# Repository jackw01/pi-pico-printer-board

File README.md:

# pi-pico-printer-board

## features

* Klipper compatible
* Uses Raspberry Pi Pico (RP2040)
* High reliability Weidmüller push-in connectors for all inputs and outputs
* 20A max and 7.5A max separately fused heater outputs
* 4x 3A max general purpose PWM outputs, individually configurable for 12V or 24V power, capable of driving inductive loads
* 3x thermistor inputs with 2.4Kohm pull up resistors
* 4x endstop inputs with one configurable for 5V or 12V operation for Z-probe
* 4x motor driver sockets
* Onboard 12V 3A and 5V 3A buck converters for powering accessories including Raspberry Pi
* Compatible with both 12V and 24V systems; components rated for 28V
* Compatible with both TMC2209 and A4988 motor drivers, and possibly others
* ESD and short-to-Vin protection on all microcontroller inputs
* Motor driver ESD and coil overvoltage protection
* Indicator LEDs for all power rails and outputs
* Alternatively supports 2.54mm pitch (Molex SL), or 2.5mm pitch (JST SM) headers for all inputs and outputs
* Labeled PCB for ease of setup and tinkering
* Open source PCB design

## design

[Schematic as PDF](pcb/rpi%20pico%20printer%20board%20rev1%2020241010.pdf)

[Sample Klipper Configuration File](klipper/printer.cfg)

[BOM (Excel)](pcb/bom.xlsx)

### license
This project is released under the CERN Open Hardware Licence Version 2 - Weakly Reciprocal (CERN-OHL-W V2).

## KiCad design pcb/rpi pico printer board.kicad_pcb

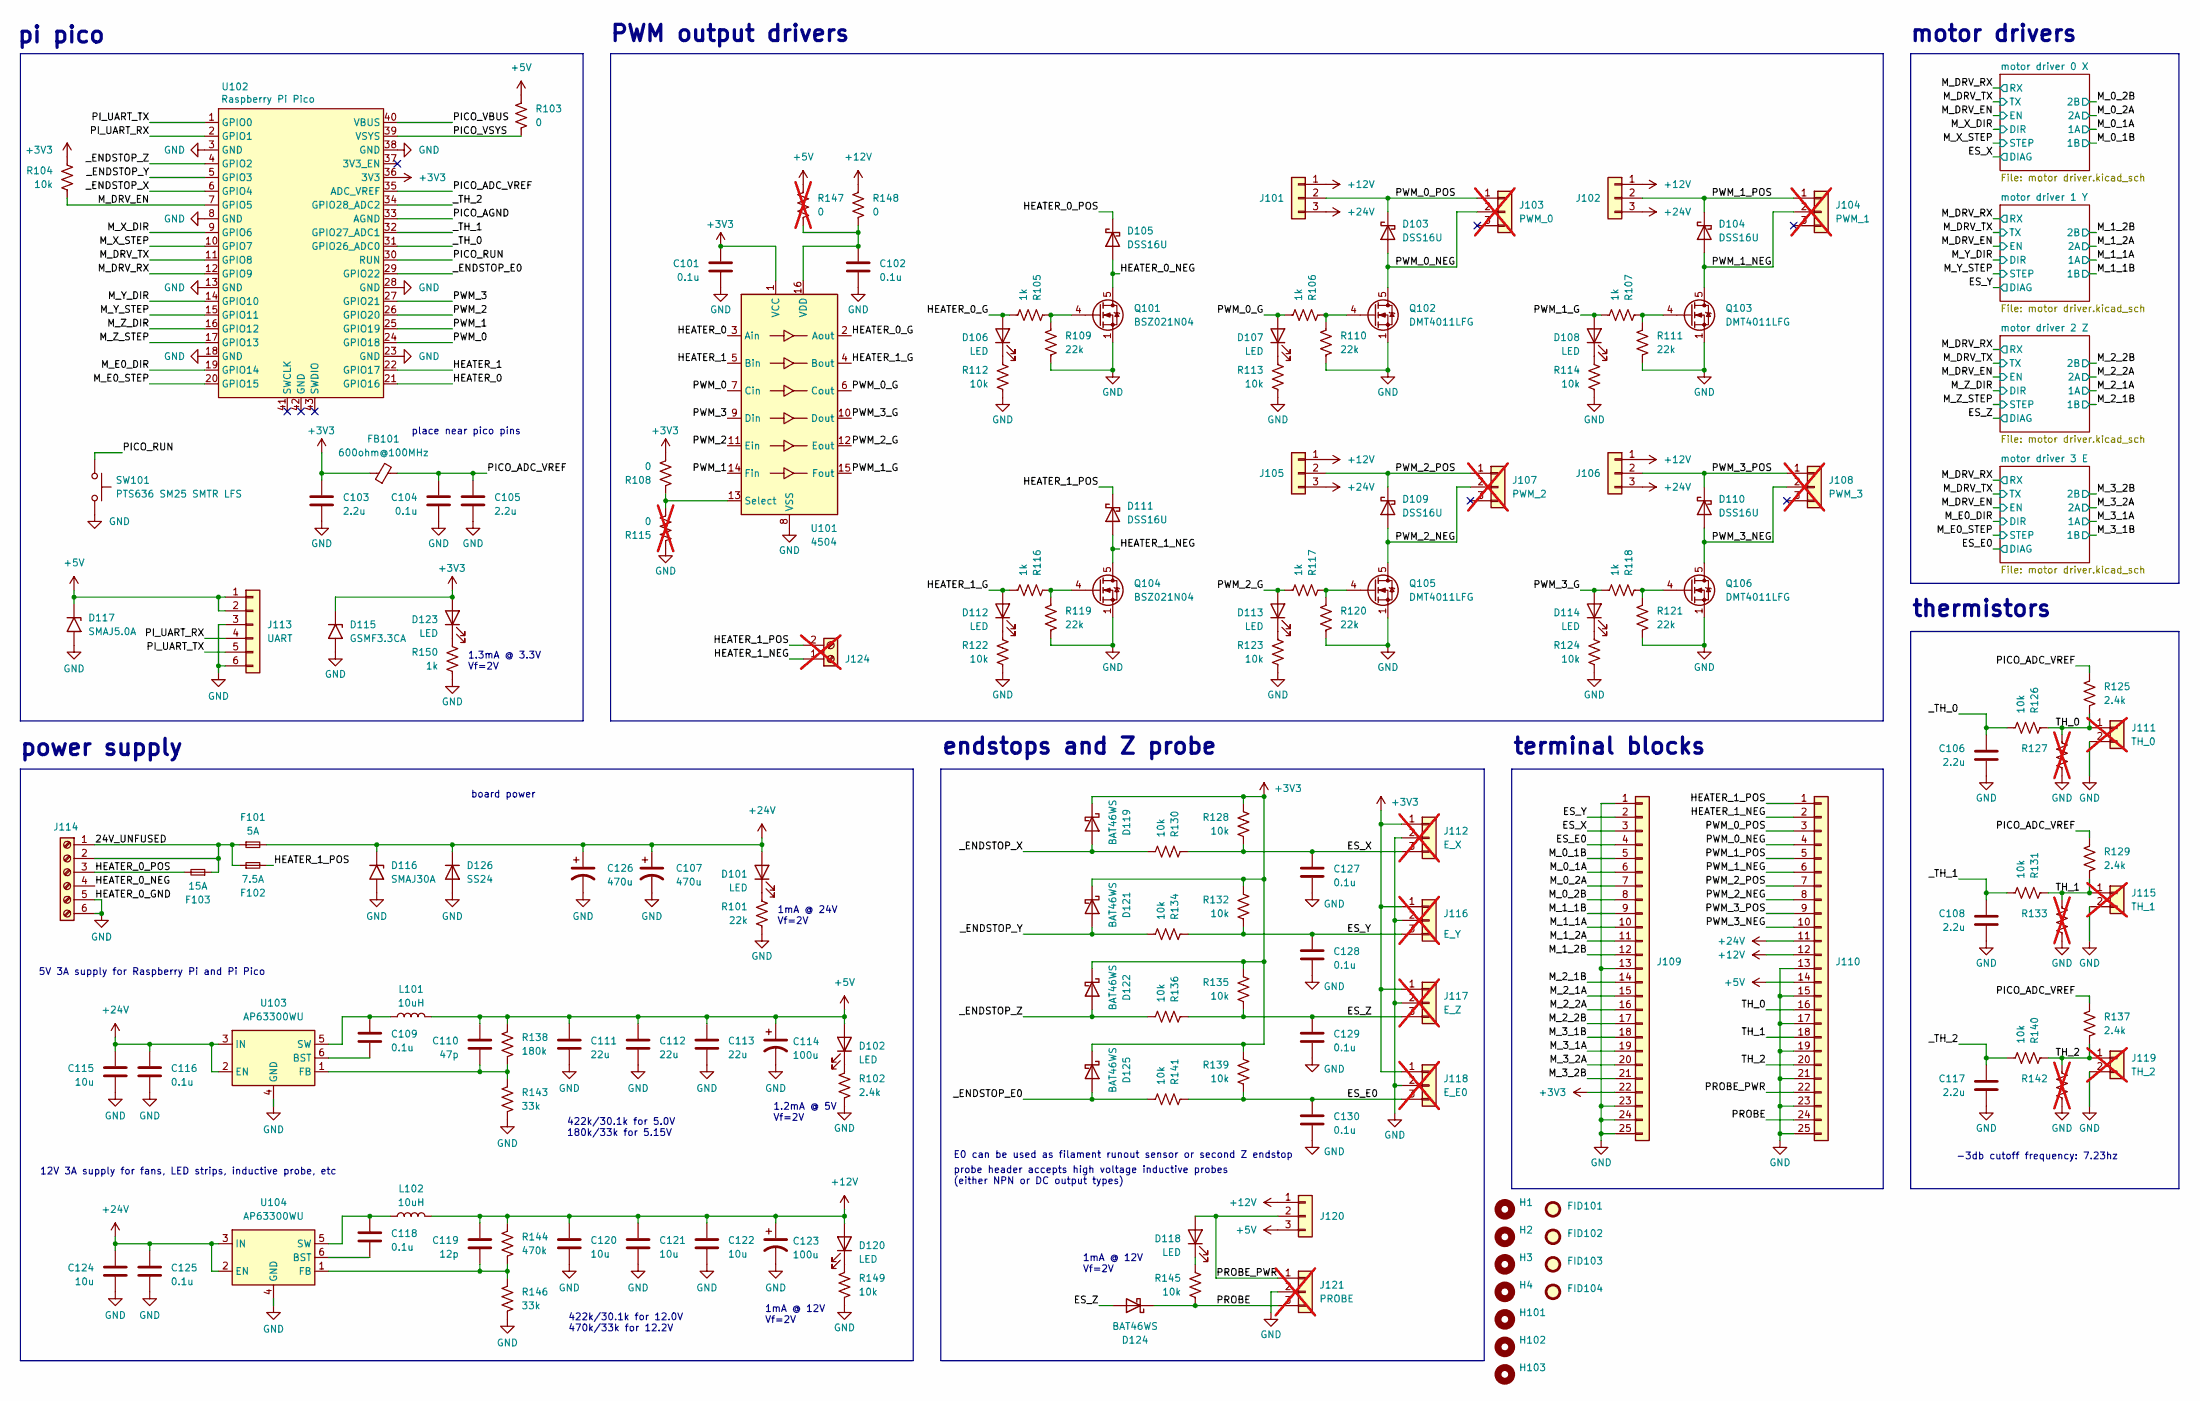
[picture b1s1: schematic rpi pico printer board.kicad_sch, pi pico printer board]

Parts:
C101, C102, C104, C109, C116, C118, C125, C127, C128, C129, C130: 0.1u; C_0603_1608Metric; MPN CL10B104KB8NNWC; JLCPCB Basic Part CC0603KRX7R9BB104
C103, C105, C106, C108, C117: 2.2u; C_0603_1608Metric; MPN CL10B225KP8NNNC; JLCPCB Basic Part CL10A225KO8NNNC
C107, C126: 470u; CP_Radial_D8.0mm_P3.50mm; MPN EEU-FR1V471L
C110: 47p; C_0603_1608Metric; MPN CL10C470JB8NNNC; JLCPCB Basic Part CL10C470JB8NNNC
C111, C112, C113: 22u; C_1210_3225Metric; MPN CL32B226KOJNNNE
C114, C123: 100u; CP_Radial_D6.3mm_P2.50mm; MPN ECA-1VM101
C115, C120, C121, C122, C124: 10u; C_1210_3225Metric; MPN CL32B106KBJNNNE
C119: 12p; C_0603_1608Metric; MPN CL10C120JB8NNNC; JLCPCB Basic Part CL10C120JB8NNNC
D101, D102, D106, D107, D108, D112, D113, D114, D118, D120, D123: LED; LED_0603_1608Metric_Pad1.05x0.95mm_HandSolder; MPN B1911UD--20D001014U1930; JLCPCB Basic Part KT-0603R
D103, D104, D105, D109, D110, D111: DSS16U; D_SOD-123F; MPN DSS16U; JLCPCB Basic Part DSK16
D115: GSMF3.3CA; D_SOD-123F; MPN GSMF3.3CA; JLCPCB Basic Part SMF3.3CA
D116: SMAJ30A; D_SMA; MPN SMAJ30A; JLCPCB Basic Part SMAJ30CA
D117: SMAJ5.0A; D_SMA; MPN SMAJ5.0A; JLCPCB Basic Part SMAJ5.0A
D119, D121, D122, D124, D125: BAT46WS; D_SOD-323; MPN BAT46WS; JLCPCB Basic Part BAT46WS
D126: SS24; D_SMA; MPN SS24; JLCPCB Basic Part SS24
F101: 5A; Fuseholder_Blade_Mini_Keystone_3568; MPN 3568
F102: 7.5A; Fuseholder_Blade_Mini_Keystone_3568; MPN 3568
F103: 15A; Fuseholder_Blade_Mini_Keystone_3568; MPN 3568
FB101: 600ohm@100MHz; L_0603_1608Metric; MPN BLM18AG601SH1D; JLCPCB Basic Part GZ1608D601TF
FID101, FID102, FID103, FID104: Fiducial_1mm_Mask2mm
H1, H2, H3, H4: MountingHole; MountingHole_3.2mm_M3_Mask
H101, H102, H103: ToolingHole; JLC_tooling_hole
J101, J102, J105, J106, J120: 2.54mm; PinHeader_1x03_P2.54mm_Vertical; MPN PH1-03-UA
J103: PWM_0; JST_XH_plus_2.54mm_01x03; not fitted
J104: PWM_1; JST_XH_plus_2.54mm_01x03; not fitted
J107: PWM_2; JST_XH_plus_2.54mm_01x03; not fitted
J108: PWM_3; JST_XH_plus_2.54mm_01x03; not fitted
J109, J110: Conn_01x25; Weidmuller_1870890000_25; MPN 1870630000
J111: TH_0; JST_XH_plus_2.54mm_01x02; not fitted
J112: E_X; JST_XH_plus_2.54mm_01x03; not fitted
J113: UART; Molex_SL_171971-0006_1x06_P2.54mm_Vertical; MPN 1719710006
J114: Screw_Terminal_01x06; Weidmuller_LMFV_5.00_06_90; MPN 2786570000
J115: TH_1; JST_XH_plus_2.54mm_01x02; not fitted
J116: E_Y; JST_XH_plus_2.54mm_01x03; not fitted
J117: E_Z; JST_XH_plus_2.54mm_01x03; not fitted
J118: E_E0; JST_XH_plus_2.54mm_01x03; not fitted
J119: TH_2; JST_XH_plus_2.54mm_01x02; not fitted
J121: PROBE; JST_XH_plus_2.54mm_01x03; not fitted
J124: Screw_Terminal_01x02; TerminalBlock_Phoenix_MKDS-1,5-2_1x02_P5.00mm_Horizontal; not fitted
L101, L102: 10uH; L_Bourns_SRN8040TA; MPN SRN8040TA-100M
Q101, Q104: BSZ021N04; Diodes_PowerDI3333-8; MPN BSZ021N04LS6ATMA1
Q102, Q103, Q105, Q106: DMT4011LFG; Diodes_PowerDI3333-8; MPN DMT4011LFG-13
R101, R109, R110, R111, R119, R120, R121: 22k; R_0603_1608Metric; JLCPCB Basic Part 0603WAF2202T5E
R102, R125, R129, R137: 2.4k; R_0603_1608Metric; JLCPCB Basic Part 0603WAF2401T5E
R103, R108, R148: 0; R_0603_1608Metric_Bridged
R104, R112, R113, R114, R122, R123, R124, R126, R128, R130, R131, R132, R134, R135, R136, R139, R140, R141, R145, R149: 10k; R_0603_1608Metric; JLCPCB Basic Part 0603WAF1002T5E
R105, R106, R107, R116, R117, R118, R150: 1k; R_0603_1608Metric; JLCPCB Basic Part 0603WAF1001T5E
R115, R147: 0; R_0603_1608Metric; not fitted
R127, R133, R142: R_0603_1608Metric; not fitted
R138: 180k; R_0603_1608Metric; JLCPCB Basic Part 0603WAF1803T5E
R143, R146: 33k; R_0603_1608Metric; JLCPCB Basic Part 0603WAF3302T5E
R144: 470k; R_0603_1608Metric; JLCPCB Basic Part 0603WAF4703T5E
SW101: PTS636 SM25 SMTR LFS; SW_SPST_CK_RS282G05A3; MPN PTS636 SM25 SMTR LFS
U101: 4504; TSSOP-16_4.4x5mm_P0.65mm; MPN CD4504BPWR
U102: Raspberry Pi Pico; RPi_Pico_SMD_minimal; MPN SC0915
U103, U104: AP63300WU; TSOT-23-6; MPN AP63300WU-7

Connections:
+3V3: C101.1, C103.1, D115.1 (A1), D119.1 (K), D121.1 (K), D122.1 (K), D123.2 (A), D125.1 (K), FB101.1, J109.22, J112.1, J116.1, J117.1, J118.1, R104.1, R108.2, R128.1, R132.1, R135.1, R139.1, U101.1 (VCC), U102.36 (3V3); also elsewhere on the board
+5V: C110.1, C111.1, C112.1, C113.1, C114.1, D102.2 (A), D117.1 (A1), J110.14, J113.1, J113.2, J120.3, L101.2, R103.1, R138.1, R147.1
+12V: C119.1, C120.1, C121.1, C122.1, C123.1, D120.2 (A), J101.1, J102.1, J105.1, J106.1, J110.12, J120.1, L102.2, R144.1, R148.1
+24V: C107.1, C115.1, C116.1, C124.1, C125.1, C126.1, D101.2 (A), D116.1 (A1), D126.1 (K), F101.2, J101.3, J102.3, J105.3, J106.3, J110.11, U103.2 (EN), U103.3 (IN), U104.2 (EN), U104.3 (IN); also elsewhere on the board
/24V_UNFUSED: F101.1, F102.1, F103.1, J114.1, J114.2
/ES_E0: C130.1, J109.4, J118.3, R139.2, R141.1; also elsewhere on the board
/ES_X: C127.1, J109.3, J112.3, R128.2, R130.1; also elsewhere on the board
/ES_Y: C128.1, J109.2, J116.3, R132.2, R134.1; also elsewhere on the board
/ES_Z: C129.1, D124.2 (A), J117.3, R135.2, R136.1; also elsewhere on the board
/HEATER_0: U101.3 (Ain), U102.21 (GPIO16)
/HEATER_0_G: D106.2 (A), R105.2, U101.2 (Aout)
/HEATER_0_NEG: D105.2 (A), J114.4, Q101.5 (D)
/HEATER_0_POS: D105.1 (K), F103.2, J114.3
/HEATER_1: U101.5 (Bin), U102.22 (GPIO17)
/HEATER_1_G: D112.2 (A), R116.2, U101.4 (Bout)
/HEATER_1_NEG: D111.2 (A), J110.2, J124.1, Q104.5 (D)
/HEATER_1_POS: D111.1 (K), F102.2, J110.1, J124.2
/M_0_1A: J109.6; also elsewhere on the board
/M_0_1B: J109.5; also elsewhere on the board
/M_0_2A: J109.7; also elsewhere on the board
/M_0_2B: J109.8; also elsewhere on the board
/M_1_1A: J109.10; also elsewhere on the board
/M_1_1B: J109.9; also elsewhere on the board
/M_1_2A: J109.11; also elsewhere on the board
/M_1_2B: J109.12; also elsewhere on the board
/M_2_1A: J109.15; also elsewhere on the board
/M_2_1B: J109.14; also elsewhere on the board
/M_2_2A: J109.16; also elsewhere on the board
/M_2_2B: J109.17; also elsewhere on the board
/M_3_1A: J109.19; also elsewhere on the board
/M_3_1B: J109.18; also elsewhere on the board
/M_3_2A: J109.20; also elsewhere on the board
/M_3_2B: J109.21; also elsewhere on the board
/M_DRV_EN: R104.2, U102.7 (GPIO5); also elsewhere on the board
/M_DRV_RX: U102.12 (GPIO9); also elsewhere on the board
/M_DRV_TX: U102.11 (GPIO8); also elsewhere on the board
/M_E0_DIR: U102.19 (GPIO14); also elsewhere on the board
/M_E0_STEP: U102.20 (GPIO15); also elsewhere on the board
/M_X_DIR: U102.9 (GPIO6); also elsewhere on the board
/M_X_STEP: U102.10 (GPIO7); also elsewhere on the board
/M_Y_DIR: U102.14 (GPIO10); also elsewhere on the board
/M_Y_STEP: U102.15 (GPIO11); also elsewhere on the board
/M_Z_DIR: U102.16 (GPIO12); also elsewhere on the board
/M_Z_STEP: U102.17 (GPIO13); also elsewhere on the board
/PICO_ADC_VREF: C104.1, C105.1, FB101.2, R125.1, R129.1, R137.1, U102.35 (ADC_VREF)
/PICO_AGND: U102.33 (AGND)
/PICO_RUN: SW101.1, U102.30 (RUN)
/PICO_VBUS: U102.40 (VBUS)
/PICO_VSYS: R103.2, U102.39 (VSYS)
/PI_UART_RX: J113.4, U102.2 (GPIO1)
/PI_UART_TX: J113.5, U102.1 (GPIO0)
/PROBE: D124.1 (K), J110.24, J121.3, R145.2
/PROBE_PWR: D118.2 (A), J110.22, J120.2, J121.1
/PWM_0: U101.7 (Cin), U102.24 (GPIO18)
/PWM_0_G: D107.2 (A), R106.2, U101.6 (Cout)
/PWM_0_NEG: D103.2 (A), J103.2, J110.4, Q102.5 (D)
/PWM_0_POS: D103.1 (K), J101.2, J103.1, J110.3
/PWM_1: U101.14 (Fin), U102.25 (GPIO19)
/PWM_1_G: D108.2 (A), R107.2, U101.15 (Fout)
/PWM_1_NEG: D104.2 (A), J104.2, J110.6, Q103.5 (D)
/PWM_1_POS: D104.1 (K), J102.2, J104.1, J110.5
/PWM_2: U101.11 (Ein), U102.26 (GPIO20)
/PWM_2_G: D113.2 (A), R117.2, U101.12 (Eout)
/PWM_2_NEG: D109.2 (A), J107.2, J110.8, Q105.5 (D)
/PWM_2_POS: D109.1 (K), J105.2, J107.1, J110.7
/PWM_3: U101.9 (Din), U102.27 (GPIO21)
/PWM_3_G: D114.2 (A), R118.2, U101.10 (Dout)
/PWM_3_NEG: D110.2 (A), J108.2, J110.10, Q106.5 (D)
/PWM_3_POS: D110.1 (K), J106.2, J108.1, J110.9
/TH_0: J110.16, J111.1, R125.2, R126.1, R127.1
/TH_1: J110.18, J115.1, R129.2, R131.1, R133.1
/TH_2: J110.20, J119.1, R137.2, R140.1, R142.1
/_ENDSTOP_E0: D125.2 (A), R141.2, U102.29 (GPIO22)
/_ENDSTOP_X: D119.2 (A), R130.2, U102.6 (GPIO4)
/_ENDSTOP_Y: D121.2 (A), R134.2, U102.5 (GPIO3)
/_ENDSTOP_Z: D122.2 (A), R136.2, U102.4 (GPIO2)
/_TH_0: C106.1, R126.2, U102.31 (GPIO26_ADC0)
/_TH_1: C108.1, R131.2, U102.32 (GPIO27_ADC1)
/_TH_2: C117.1, R140.2, U102.34 (GPIO28_ADC2)
GND: C101.2, C102.2, C103.2, C104.2, C105.2, C106.2, C107.2, C108.2, C111.2, C112.2, C113.2, C114.2, C115.2, C116.2, C117.2, C120.2, C121.2, C122.2, C123.2, C124.2, C125.2, C126.2, C127.2, C128.2, C129.2, C130.2, D115.2 (A2), D116.2 (A2), D117.2 (A2), D126.2 (A), J109.1, J109.13, J109.23, J109.24, J109.25, J110.13, J110.15, J110.17, J110.19, J110.21, J110.23, J110.25, J111.2, J112.2, J113.3, J113.6, J114.5, J114.6, J115.2, J116.2, J117.2, J118.2, J119.2, J121.2, Q101.1 (S), Q101.2 (S), Q101.3 (S), Q102.1 (S), Q102.2 (S), Q102.3 (S), Q103.1 (S), Q103.2 (S), Q103.3 (S), Q104.1 (S), Q104.2 (S), Q104.3 (S), Q105.1 (S), Q105.2 (S), Q105.3 (S), Q106.1 (S), Q106.2 (S), Q106.3 (S), R101.2, R102.2, R109.2, R110.2, R111.2, R112.2, R113.2, R114.2, R115.1, R119.2, R120.2, R121.2, R122.2, R123.2, R124.2, R127.2, R133.2, R142.2, R143.2, R146.2, R149.2, R150.2, SW101.2, U101.8 (VSS), U102.3 (GND), U102.8 (GND), U102.13 (GND), U102.18 (GND), U102.23 (GND), U102.28 (GND), U102.38 (GND), U103.4 (GND), U104.4 (GND); also elsewhere on the board
unnamed: D101.1 (K), R101.1
unnamed: D102.1 (K), R102.1
unnamed: D106.1 (K), R112.1
unnamed: D107.1 (K), R113.1
unnamed: D108.1 (K), R114.1
unnamed: D112.1 (K), R122.1
unnamed: D113.1 (K), R123.1
unnamed: D114.1 (K), R124.1
unnamed: D118.1 (K), R145.1
unnamed: D120.1 (K), R149.1
unnamed: D123.1 (K), R150.1
unnamed: Q101.4 (G), R105.1, R109.1
unnamed: Q102.4 (G), R106.1, R110.1
unnamed: Q103.4 (G), R107.1, R111.1
unnamed: Q104.4 (G), R116.1, R119.1
unnamed: Q105.4 (G), R117.1, R120.1
unnamed: Q106.4 (G), R118.1, R121.1
unnamed: R108.1, R115.2, U101.13 (Select)
unnamed: C102.1, R147.2, R148.2, U101.16 (VDD)
unnamed: C109.2, U103.6 (BST)
unnamed: C110.2, R138.2, R143.1, U103.1 (FB)
unnamed: C109.1, L101.1, U103.5 (SW)
unnamed: C118.2, U104.6 (BST)
unnamed: C119.2, R144.2, R146.1, U104.1 (FB)
unnamed: C118.1, L102.1, U104.5 (SW)

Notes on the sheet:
12V 3A supply for fans, LED strips, inductive probe, etc
motor drivers
PWM output drivers
1.2mA @ 5V Vf=2V
E0 can be used as filament runout sensor or second Z endstop
1.3mA @ 3.3V Vf=2V
board power
5V 3A supply for Raspberry Pi and Pi Pico
422k/30.1k for 12.0V 470k/33k for 12.2V
power supply
thermistors
terminal blocks
probe header accepts high voltage inductive probes (either NPN or DC output types)
1mA @ 12V Vf=2V
place near pico pins
1mA @ 24V Vf=2V
-3db cutoff frequency: 7.23hz
pi pico
endstops and Z probe
422k/30.1k for 5.0V 180k/33k for 5.15V

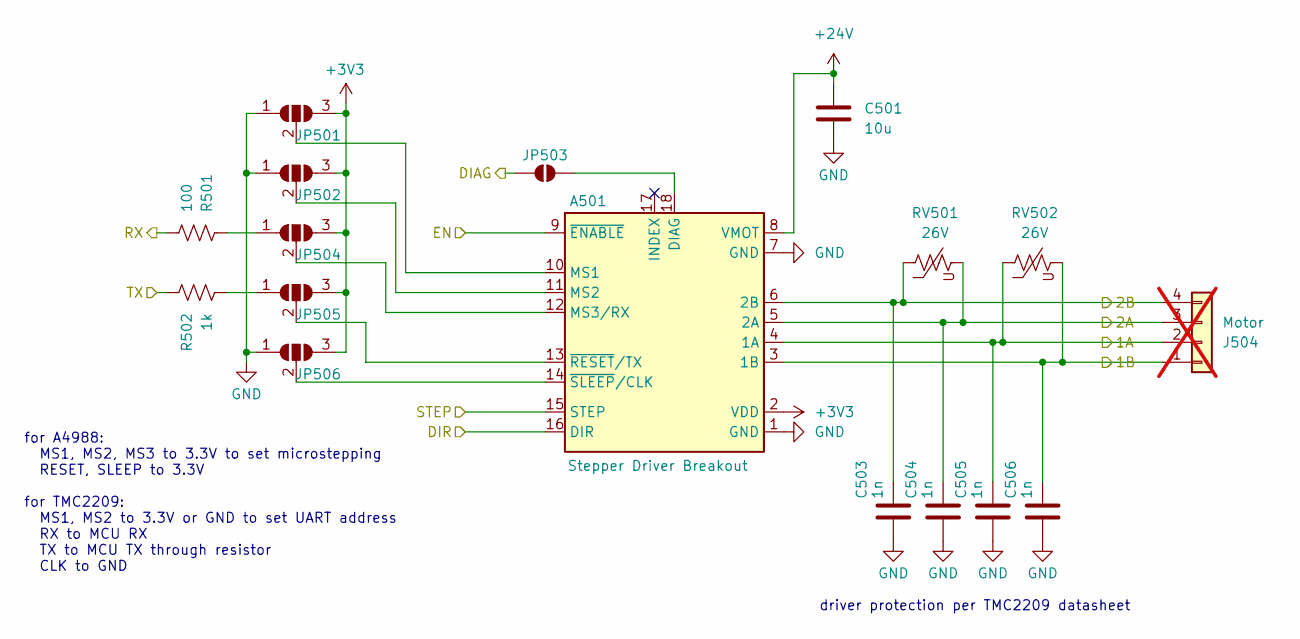
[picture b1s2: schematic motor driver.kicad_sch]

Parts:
A501: Stepper Driver Breakout; BTT_TMC2209_Breakout-16_15.2x20.3mm; MPN RS1-08-G
C501: 10u; C_1210_3225Metric; MPN CL32B106KBJNNNE
C503, C504, C505, C506: 1n; C_0603_1608Metric; MPN CL10B102KB8NNNC; JLCPCB Basic Part CL10B102KB8NNNC
J504: Motor; JST_XH_plus_2.54mm_01x04; not fitted
JP501, JP502, JP504, JP505, JP506: SolderJumper_3_Open; Bi_0603_Open
JP503: SolderJumper_2_Open; Jumper_0603
R501: 100; R_0603_1608Metric; JLCPCB Basic Part 0603WAF1000T5E
R502: 1k; R_0603_1608Metric; JLCPCB Basic Part 0603WAF1001T5E
RV501, RV502: 26V; L_1206_3216Metric; MPN ZV20K1206201NIR1

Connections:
+3V3: A501.2 (VDD), JP501.3 (B), JP502.3 (B), JP504.3 (B), JP505.3 (B), JP506.3 (B); also elsewhere on the board
+24V: A501.8 (VMOT), C501.1; also elsewhere on the board
/ES_E0: JP503.1 (A); also elsewhere on the board
/M_3_1A: A501.4 (1A), C505.2, J504.2, RV502.1; also elsewhere on the board
/M_3_1B: A501.3 (1B), C506.2, J504.1, RV502.2; also elsewhere on the board
/M_3_2A: A501.5 (2A), C504.2, J504.3, RV501.2; also elsewhere on the board
/M_3_2B: A501.6 (2B), C503.2, J504.4, RV501.1; also elsewhere on the board
/M_DRV_EN: A501.9 (~ENABLE); also elsewhere on the board
/M_DRV_RX: R501.2; also elsewhere on the board
/M_DRV_TX: R502.1; also elsewhere on the board
/M_E0_DIR: A501.16 (DIR); also elsewhere on the board
/M_E0_STEP: A501.15 (STEP); also elsewhere on the board
GND: A501.1 (GND), A501.7 (GND), C501.2, C503.1, C504.1, C505.1, C506.1, JP501.1 (A), JP502.1 (A), JP506.1 (A); also elsewhere on the board
unnamed: A501.18 (DIAG), JP503.2 (B)
unnamed: A501.10 (MS1), JP501.2 (C)
unnamed: A501.11 (MS2), JP502.2 (C)
unnamed: A501.12 (MS3/RX), JP504.2 (C)
unnamed: A501.13 (~RESET/TX), JP505.2 (C)
unnamed: A501.14 (~SLEEP/CLK), JP506.2 (C)
unnamed: JP504.1 (A), R501.1
unnamed: JP505.1 (A), R502.2

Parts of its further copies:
A201, A301, A401: Stepper Driver Breakout; BTT_TMC2209_Breakout-16_15.2x20.3mm; MPN RS1-08-G
C201, C301, C401: 10u; C_1210_3225Metric; MPN CL32B106KBJNNNE
C203, C204, C205, C206, C303, C304, C305, C306, C403, C404, C405, C406: 1n; C_0603_1608Metric; MPN CL10B102KB8NNNC; JLCPCB Basic Part CL10B102KB8NNNC
J204, J304, J404: Motor; JST_XH_plus_2.54mm_01x04; not fitted
JP201, JP202, JP204, JP205, JP206, JP301, JP302, JP304, JP305, JP306, JP401, JP402, JP404, JP405, JP406: SolderJumper_3_Open; Bi_0603_Open
JP203, JP303, JP403: SolderJumper_2_Open; Jumper_0603
R201, R301, R401: 100; R_0603_1608Metric; JLCPCB Basic Part 0603WAF1000T5E
R202, R302, R402: 1k; R_0603_1608Metric; JLCPCB Basic Part 0603WAF1001T5E
RV201, RV202, RV301, RV302, RV401, RV402: 26V; L_1206_3216Metric; MPN ZV20K1206201NIR1

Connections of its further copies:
+3V3: A201.2 (VDD), A301.2 (VDD), A401.2 (VDD), JP201.3 (B), JP202.3 (B), JP204.3 (B), JP205.3 (B), JP206.3 (B), JP301.3 (B), JP302.3 (B), JP304.3 (B), JP305.3 (B), JP306.3 (B), JP401.3 (B), JP402.3 (B), JP404.3 (B), JP405.3 (B), JP406.3 (B); also elsewhere on the board
+24V: A201.8 (VMOT), A301.8 (VMOT), A401.8 (VMOT), C201.1, C301.1, C401.1; also elsewhere on the board
/ES_X: JP203.1 (A); also elsewhere on the board
/ES_Y: JP303.1 (A); also elsewhere on the board
/ES_Z: JP403.1 (A); also elsewhere on the board
/M_0_1A: A201.4 (1A), C205.2, J204.2, RV202.1; also elsewhere on the board
/M_0_1B: A201.3 (1B), C206.2, J204.1, RV202.2; also elsewhere on the board
/M_0_2A: A201.5 (2A), C204.2, J204.3, RV201.2; also elsewhere on the board
/M_0_2B: A201.6 (2B), C203.2, J204.4, RV201.1; also elsewhere on the board
/M_1_1A: A301.4 (1A), C305.2, J304.2, RV302.1; also elsewhere on the board
/M_1_1B: A301.3 (1B), C306.2, J304.1, RV302.2; also elsewhere on the board
/M_1_2A: A301.5 (2A), C304.2, J304.3, RV301.2; also elsewhere on the board
/M_1_2B: A301.6 (2B), C303.2, J304.4, RV301.1; also elsewhere on the board
/M_2_1A: A401.4 (1A), C405.2, J404.2, RV402.1; also elsewhere on the board
/M_2_1B: A401.3 (1B), C406.2, J404.1, RV402.2; also elsewhere on the board
/M_2_2A: A401.5 (2A), C404.2, J404.3, RV401.2; also elsewhere on the board
/M_2_2B: A401.6 (2B), C403.2, J404.4, RV401.1; also elsewhere on the board
/M_DRV_EN: A201.9 (~ENABLE), A301.9 (~ENABLE), A401.9 (~ENABLE); also elsewhere on the board
/M_DRV_RX: R201.2, R301.2, R401.2; also elsewhere on the board
/M_DRV_TX: R202.1, R302.1, R402.1; also elsewhere on the board
/M_X_DIR: A201.16 (DIR); also elsewhere on the board
/M_X_STEP: A201.15 (STEP); also elsewhere on the board
/M_Y_DIR: A301.16 (DIR); also elsewhere on the board
/M_Y_STEP: A301.15 (STEP); also elsewhere on the board
/M_Z_DIR: A401.16 (DIR); also elsewhere on the board
/M_Z_STEP: A401.15 (STEP); also elsewhere on the board
GND: A201.1 (GND), A201.7 (GND), A301.1 (GND), A301.7 (GND), A401.1 (GND), A401.7 (GND), C201.2, C203.1, C204.1, C205.1, C206.1, C301.2, C303.1, C304.1, C305.1, C306.1, C401.2, C403.1, C404.1, C405.1, C406.1, JP201.1 (A), JP202.1 (A), JP206.1 (A), JP301.1 (A), JP302.1 (A), JP306.1 (A), JP401.1 (A), JP402.1 (A), JP406.1 (A); also elsewhere on the board
unnamed: A201.18 (DIAG), JP203.2 (B)
unnamed: A201.10 (MS1), JP201.2 (C)
unnamed: A201.11 (MS2), JP202.2 (C)
unnamed: A201.12 (MS3/RX), JP204.2 (C)
unnamed: A201.13 (~RESET/TX), JP205.2 (C)
unnamed: A201.14 (~SLEEP/CLK), JP206.2 (C)
unnamed: A301.18 (DIAG), JP303.2 (B)
unnamed: A301.10 (MS1), JP301.2 (C)
unnamed: A301.11 (MS2), JP302.2 (C)
unnamed: A301.12 (MS3/RX), JP304.2 (C)
unnamed: A301.13 (~RESET/TX), JP305.2 (C)
unnamed: A301.14 (~SLEEP/CLK), JP306.2 (C)
unnamed: A401.18 (DIAG), JP403.2 (B)
unnamed: A401.10 (MS1), JP401.2 (C)
unnamed: A401.11 (MS2), JP402.2 (C)
unnamed: A401.12 (MS3/RX), JP404.2 (C)
unnamed: A401.13 (~RESET/TX), JP405.2 (C)
unnamed: A401.14 (~SLEEP/CLK), JP406.2 (C)
unnamed: JP204.1 (A), R201.1
unnamed: JP205.1 (A), R202.2
unnamed: JP304.1 (A), R301.1
unnamed: JP305.1 (A), R302.2
unnamed: JP404.1 (A), R401.1
unnamed: JP405.1 (A), R402.2

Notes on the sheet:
driver protection per TMC2209 datasheet
for A4988: MS1, MS2, MS3 to 3.3V to set microstepping RESET, SLEEP to 3.3V for TMC2209: MS1, MS2 to 3.3V or GND to set UART address RX to MCU RX TX to MCU TX through resistor CLK to GND

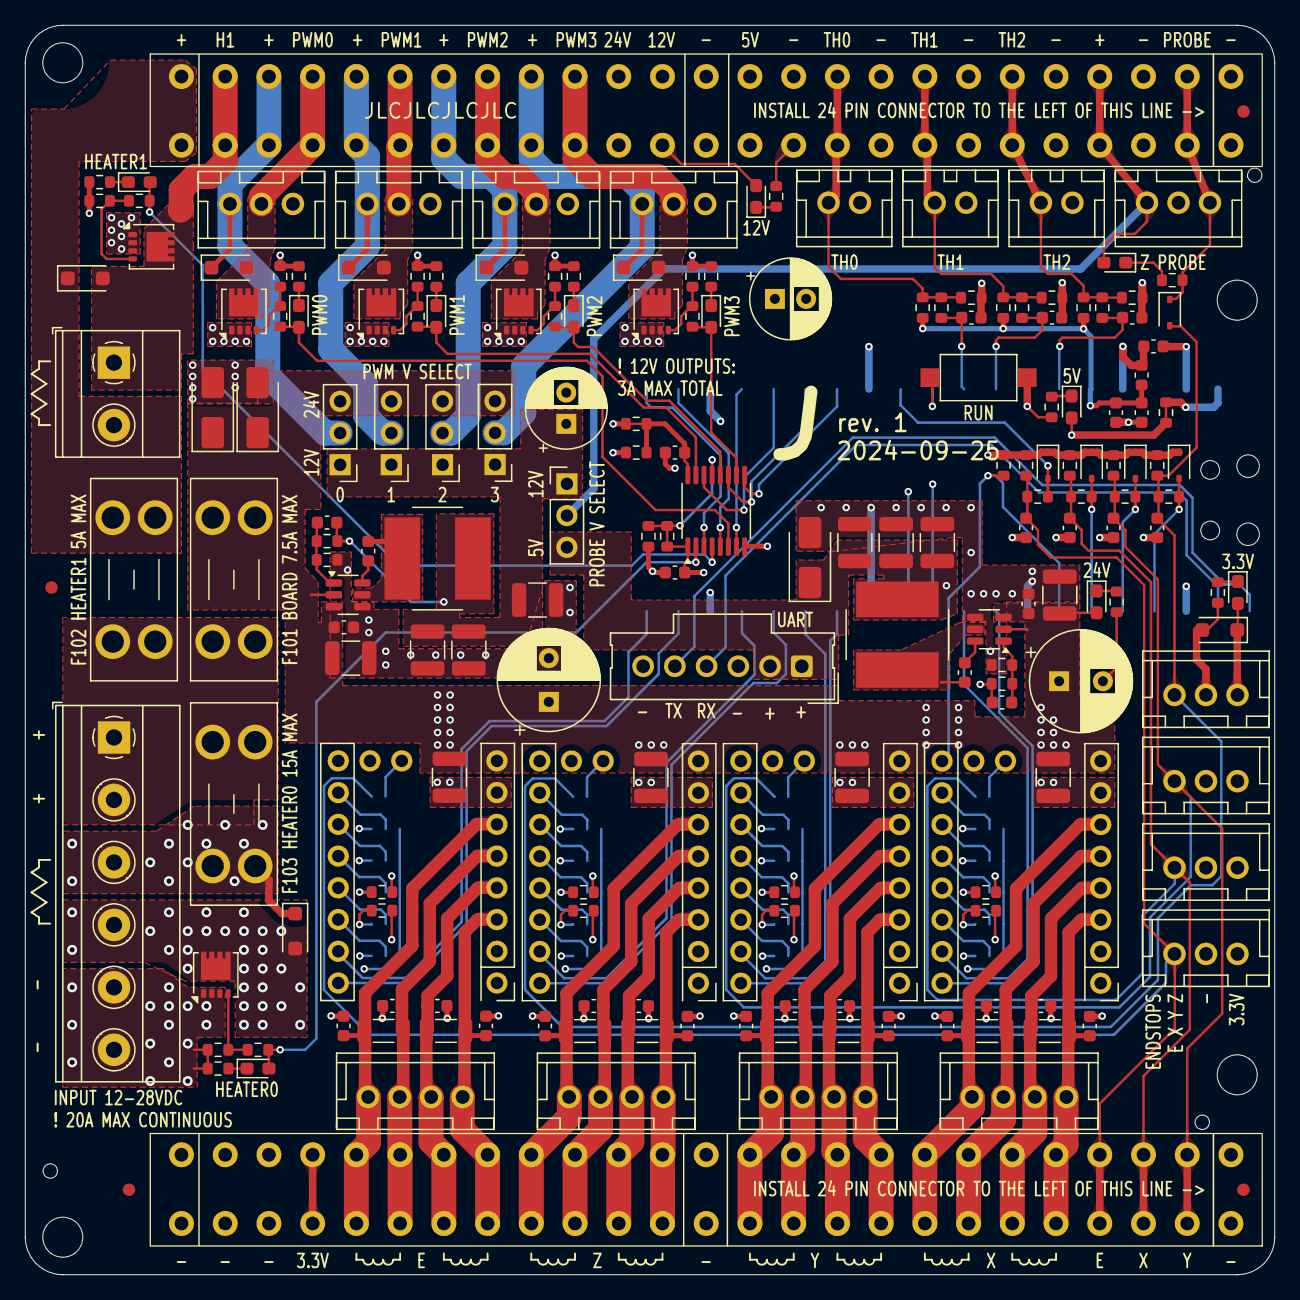
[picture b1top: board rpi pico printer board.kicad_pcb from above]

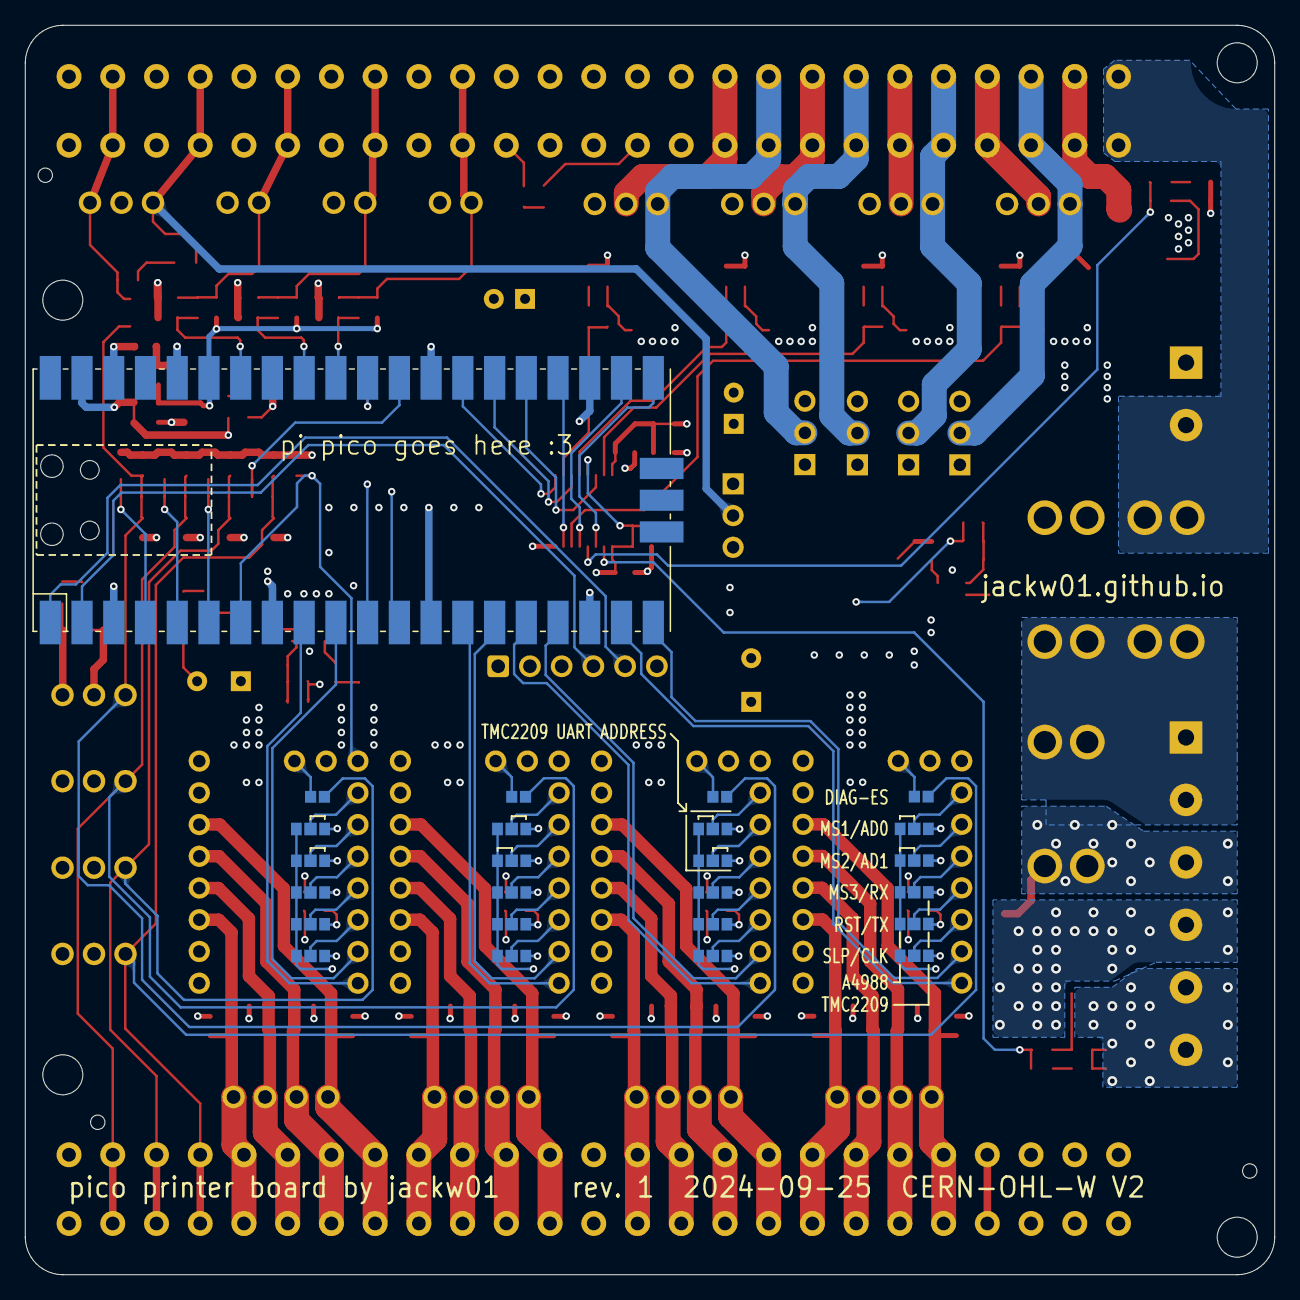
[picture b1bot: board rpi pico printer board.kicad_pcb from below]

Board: 4 copper layers, 100.0 x 100.0 mm, 224 parts (25 on the bottom side), 135 nets.

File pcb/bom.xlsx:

|  |  |  |  | 168 | 25 |  |  |  |  | 48.148500000000006 |  |  | 123.97999999999999
Reference | Value | Datasheet | Footprint | SMT | Qty | Qty THT | DNP | MPN | JLCPCB Basic/ExtPref | Cost | Ext. Cost Per Board | MOQ | Already Have? | Order Cost
A201,A301,A401,A501 | Stepper Driver Breakout | ~ | Custom:BTT_TMC2209_Breakout-16_15.2x20.3mm |  | 8 | 8 |  | RS1-08-G |  | 0.43 | 3.44 | 17 |  | 7.31
C101,C102,C104,C109,C116,C118,C125,C127,C128,C129,C130 | 0.1u | ~ | Capacitor_SMD:C_0603_1608Metric | Y | 11 | 0 |  | CL10B104KB8NNWC | CC0603KRX7R9BB104 | 7.9000000000000008E-3 | 8.6900000000000005E-2 | 100 |  | 0
C103,C105,C106,C108,C117 | 2.2u | ~ | Capacitor_SMD:C_0603_1608Metric | Y | 5 | 0 |  | CL10B225KP8NNNC | CL10A225KO8NNNC | 4.1000000000000002E-2 | 0.20500000000000002 | 50 |  | 0
C107,C126 | 470u | ~ | Capacitor_THT:CP_Radial_D8.0mm_P3.50mm |  | 2 | 2 |  | EEU-FR1V471L |  | 0.45100000000000001 | 0.90200000000000002 | 10 |  | 4.51
C110 | 47p | ~ | Capacitor_SMD:C_0603_1608Metric | Y | 1 | 0 |  | CL10C470JB8NNNC | CL10C470JB8NNNC | 3.4000000000000002E-2 | 3.4000000000000002E-2 | 10 |  | 0
C111,C112,C113 | 22u | ~ | Capacitor_SMD:C_1210_3225Metric | Y | 3 | 0 |  | CL32B226KOJNNNE |  | 0.29499999999999998 | 0.88500000000000001 | 10 |  | 2.9499999999999997
C114,C123 | 100u | ~ | Capacitor_THT:CP_Radial_D6.3mm_P2.50mm |  | 2 | 2 |  | ECA-1VM101 |  | 0.19 | 0.38 | 10 |  | 1.9
C115,C120,C121,C122,C124,C201,C301,C401,C501 | 10u | ~ | Capacitor_SMD:C_1210_3225Metric | Y | 9 | 0 |  | CL32B106KBJNNNE |  | 0.28060000000000002 | 2.5254000000000003 | 50 |  | 14.030000000000001
C119 | 12p | ~ | Capacitor_SMD:C_0603_1608Metric | Y | 1 | 0 |  | CL10C120JB8NNNC | CL10C120JB8NNNC | 2.1999999999999999E-2 | 2.1999999999999999E-2 | 10 |  | 0
C203,C204,C205,C206,C303,C304,C305,C306,C403,C404,C405,C406,C503,C504,C505,C506 | 1n | ~ | Capacitor_SMD:C_0603_1608Metric | Y | 16 | 0 |  | CL10B102KB8NNNC | CL10B102KB8NNNC | 1.2200000000000001E-2 | 0.19520000000000001 | 100 |  | 0
D101,D102,D106,D107,D108,D112,D113,D114,D118,D120,D123 | LED | ~ | LED_SMD:LED_0603_1608Metric_Pad1.05x0.95mm_HandSolder | Y | 11 | 0 |  | B1911UD--20D001014U1930 | KT-0603R | 4.7E-2 | 0.51700000000000002 | 10 |  | 0
D103,D104,D105,D109,D110,D111 | DSS16U | ~ | Diode_SMD:D_SOD-123 | Y | 6 | 0 |  | DSS16U | DSK16 | 0.11899999999999999 | 0.71399999999999997 | 10 |  | 0
D115 | D3V3AP2W | ~ | Diode_SMD:D_SOD-123 | Y | 1 | 0 |  | GSMF3.3CA |  | 0.13400000000000001 | 0.13400000000000001 | 10 |  | 1.34
D116 | SMAJ30A | ~ | Diode_SMD:D_SMA | Y | 1 | 0 |  | SMAJ30A | SMAJ30CA | 0.39 | 0.39 | 1 |  | 0
D117 | SMAJ5.0A | ~ | Diode_SMD:D_SMA | Y | 1 | 0 |  | SMAJ5.0A | SMAJ5.0A | 0.39 | 0.39 | 1 |  | 0
D119,D121,D122,D124,D125 | BAT46WS | ~ | Diode_SMD:D_SOD-323 | Y | 5 | 0 |  | BAT46WS | BAT46WS | 0.13900000000000001 | 0.69500000000000006 | 10 |  | 0
D126 | SS24 | ~ | Diode_SMD:D_SMA | Y | 1 | 0 |  | SS24 | SS24 | 0.26700000000000002 | 0.26700000000000002 | 10 |  | 0
F101 | 5A | ~ | Fuse:Fuseholder_Blade_Mini_Keystone_3568 |  | 1 | 1 |  | 3568 |  | 1.31 | 1.31 | 1 |  | 2.62
F102 | 7.5A | ~ | Fuse:Fuseholder_Blade_Mini_Keystone_3568 |  | 1 | 1 |  | 3568 |  | 1.31 | 1.31 | 1 |  | 2.62
F103 | 15A | ~ | Fuse:Fuseholder_Blade_Mini_Keystone_3568 |  | 1 | 1 |  | 3568 |  | 1.31 | 1.31 | 1 |  | 2.62
FB101 | 600ohm@100MHz | ~ | Inductor_SMD:L_0603_1608Metric | Y | 1 | 0 |  | BLM18AG601SH1D | GZ1608D601TF | 7.0999999999999994E-2 | 7.0999999999999994E-2 | 10 |  | 0
J101,J102,J105,J106,J120 | 2.54mm | ~ | Connector_PinHeader_2.54mm:PinHeader_1x03_P2.54mm_Vertical |  | 5 | 5 |  | PH1-03-UA |  | 4.7E-2 | 0.23499999999999999 | 10 |  | 0.47
J109,J110 | Conn_01x25 | ~ | Custom:Weidmuller_1870890000_25 |  | 2 | 2 |  | 1870630000 |  | 5.55 | 11.1 | 1 |  | 22.2
J113 | UART | ~ | Custom:Molex_SL_171971-0006_1x06_P2.54mm_Vertical |  | 1 | 1 |  | 1719710006 |  | 1.43 | 1.43 | 1 |  | 2.86
J114 | Screw_Terminal_01x06 | ~ | Custom:Weidmuller_LMFV_5.00_06_90 |  | 1 | 1 |  | 2786570000 |  | 4.26 | 4.26 | 1 |  | 8.52
L101,L102 | 10uH | ~ | Custom:L_Bourns_SRN8040TA | Y | 2 | 0 |  | SRN8040TA-100M |  | 0.55200000000000005 | 1.1040000000000001 | 10 |  | 5.5200000000000005
Q101,Q104 | BSZ021N04 |  | Package_SON:Diodes_PowerDI3333-8 | Y | 2 | 0 |  | BSZ021N04LS6ATMA1 |  | 1.5660000000000001 | 3.1320000000000001 | 10 |  | 15.66
Q102,Q103,Q105,Q106 | DMT4011LFG |  | Package_SON:Diodes_PowerDI3333-8 | Y | 4 | 0 |  | DMT4011LFG-13 |  | 0.442 | 1.768 | 10 |  | 4.42
R101,R109,R110,R111,R119,R120,R121 | 22k | ~ | Resistor_SMD:R_0603_1608Metric | Y | 7 | 0 |  |  | 0603WAF2202T5E | 7.7999999999999996E-3 | 5.4599999999999996E-2 | 50 |  | 0
R102,R125,R129,R137 | 2.49k | ~ | Resistor_SMD:R_0603_1608Metric | Y | 4 | 0 |  |  | 0603WAF2401T5E | 7.7999999999999996E-3 | 3.1199999999999999E-2 | 50 |  | 0
R104,R112,R113,R114,R122,R123,R124,R126,R128,R130,R131,R132,R134,R135,R136,R139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 | 10k | ~ | Resistor_SMD:R_0603_1608Metric | Y | 20 | 0 |  |  | 0603WAF1002T5E | 7.7999999999999996E-3 | 0.156 | 50 |  | 0
R105,R106,R107,R116,R117,R118,R150,R202,R302,R402,R502 | 1k | ~ | Resistor_SMD:R_0603_1608Metric | Y | 11 | 0 |  |  | 0603WAF1001T5E | 7.7999999999999996E-3 | 8.5800000000000001E-2 | 50 |  | 0
R138 | 172k | ~ | Resistor_SMD:R_0603_1608Metric | Y | 1 | 0 |  |  | 0603WAF1803T5E | 7.7999999999999996E-3 | 7.7999999999999996E-3 | 50 |  | 0
R143,R146 | 31.6k | ~ | Resistor_SMD:R_0603_1608Metric | Y | 2 | 0 |  |  | 0603WAF3302T5E | 7.7999999999999996E-3 | 1.5599999999999999E-2 | 50 |  | 0
R144 | 475k | ~ | Resistor_SMD:R_0603_1608Metric | Y | 1 | 0 |  |  | 0603WAF4703T5E | 7.7999999999999996E-3 | 7.7999999999999996E-3 | 50 |  | 0
R201,R301,R401,R501 | 100 | ~ | Resistor_SMD:R_0603_1608Metric | Y | 4 | 0 |  |  | 0603WAF1000T5E | 7.7999999999999996E-3 | 3.1199999999999999E-2 | 50 |  | 0
RV201,RV202,RV301,RV302,RV401,RV402,RV501,RV502 | 26V | ~ | Inductor_SMD:L_1206_3216Metric | Y | 8 | 0 |  | ZV25K1206201NIR1 |  | 0.29799999999999999 | 2.3839999999999999 | 25 |  | 7.4499999999999993
SW101 | PTS636 SM25 SMTR LFS | ~ | Button_Switch_SMD:SW_SPST_CK_RS282G05A3 | Y | 1 | 0 |  | PTS636 SM25 SMTR LFS |  | 0.24 | 0.24 | 1 |  | 0.48
U101 | 4504 | ~ | Package_SO:TSSOP-16_4.4x5mm_P0.65mm | Y | 1 | 0 |  | CD4504BPWR |  | 0.48199999999999998 | 0.48199999999999998 | 10 |  | 4.82
U102 | Raspberry Pi Pico | ~ | Custom:RPi_Pico_SMD_minimal |  | 1 | 1 |  | SC0915 |  | 4 | 4 | 1 |  | 8
U103,U104 | AP63300WU | https://www.diodes.com/assets/Datasheets/AP63300-AP63301.pdf | Package_TO_SOT_SMD:TSOT-23-6 | Y | 2 | 0 |  | AP63300WU-7 |  | 0.92 | 1.84 | 1 |  | 3.68

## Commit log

2024-11-23 publish
2024-11-23 add BOM link
2025-03-06 Update LICENSE

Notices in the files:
pcb/rpi pico printer board.kicad_pcb:
pico printer board by jackw01 rev. 1  2024-09-25  CERN-OHL-W V2
Released under the CERN-OHL-W V2 license
